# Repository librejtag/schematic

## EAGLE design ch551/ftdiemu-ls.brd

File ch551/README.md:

LibreJTAG Dongle based on CH551. Drawn by EAGLE.

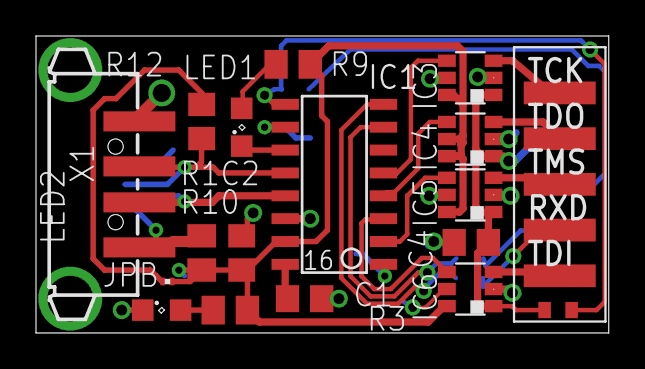
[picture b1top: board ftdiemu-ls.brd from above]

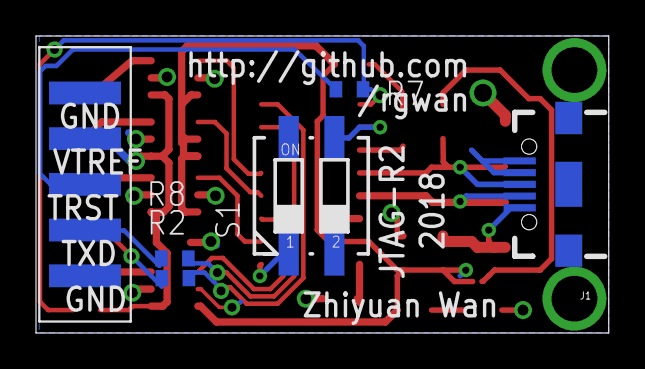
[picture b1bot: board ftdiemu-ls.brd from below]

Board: 2 copper layers, 31.8 x 16.5 mm, 24 parts (6 on the bottom side), 27 nets.

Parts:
C1, C4: 100n; C0805
C2: 10u; C0805
CON1, CON2: SIDESMT
IC1: CH551G-16L; SO-16
IC3, IC4, IC5, IC6: 741T45W6; DBV_R-PDSO-G6
J1: USB-MICROB"; USB-B-MICRO-SMD_V03
JPB: JP; R0201
LED1, LED2: SML0805
R1: 100mA FUSE; M0805
R2, R8: 22; R0402
R3, R7: 22/680; R0402
R9, R10: 2.2k; M0805
R12: 20k; R0805
S1: 219-02J; CTS-219-02J
X1: USB-A003

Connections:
+3V3: C1.1, IC1.16
+5V: C2.1, IC1.15, IC3.6, IC4.5, IC4.6, IC5.6, IC6.6, JPB.2, R1.2, R9.2, R10.2
DM: IC1.13, J1.D-, X1.3
DP: IC1.12, J1.D+, R12.1, X1.2
FUNC_SEL0: IC1.10, S1.3
FUNC_SEL1: IC1.1, S1.1
GND: C1.2, C2.2, C4.2, CON2.1, CON2.5, IC1.14, IC3.2, IC3.5, IC4.2, IC5.2, IC5.5, IC6.2, IC6.5, J1.GND, J1.ID, J1.SHIELD1, J1.SHIELD2, J1.SHIELD3, LED2.C, S1.2, S1.4, X1.1
JTAG_RST: IC1.9, R3.2, R7.2
JTAG_TCK: IC1.5, IC3.4
JTAG_TDI: IC1.3, IC6.4
JTAG_TDO: IC1.4, IC4.4
JTAG_TMS: IC1.2, IC5.4
LED: IC1.11, LED1.C
unnamed: CON1.5, IC3.3
unnamed: CON1.4, IC4.3
unnamed: CON1.3, IC5.3
unnamed: CON1.2, R2.1
unnamed: CON1.1, IC6.3
unnamed: CON2.3, R7.1
unnamed: CON2.2, R8.1
unnamed: LED1.A, R9.1
unnamed: LED2.A, R10.1
unnamed: JPB.1, R12.2
RESERVE1: IC1.8, R2.2
RESERVE2: IC1.7, R8.2
VBUS: J1.VBUS, R1.1, X1.4
VCCINT: C4.1, CON2.4, IC3.1, IC4.1, IC5.1, IC6.1, R3.1

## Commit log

2018-01-25 Import Schematic

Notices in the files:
parts and their libraries:
SparkFun-Connectors: Licensing: Creative Commons ShareAlike 4.0 International - https://creativecommons.org/licenses/by-sa/4.0
